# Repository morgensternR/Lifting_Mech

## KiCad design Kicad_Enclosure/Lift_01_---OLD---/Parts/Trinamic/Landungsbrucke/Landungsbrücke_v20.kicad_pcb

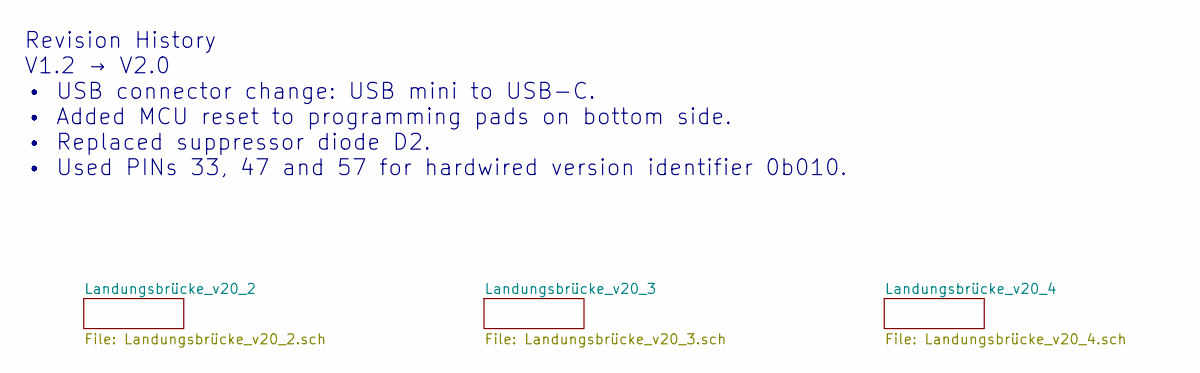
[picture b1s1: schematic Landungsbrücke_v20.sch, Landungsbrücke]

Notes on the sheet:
Revision History V1.2 → V2.0 • USB connector change: USB mini to USB-C. • Added MCU reset to programming pads on bottom side. • Replaced suppressor diode D2. • Used PINs 33, 47 and 57 for hardwired version identifier 0b010.

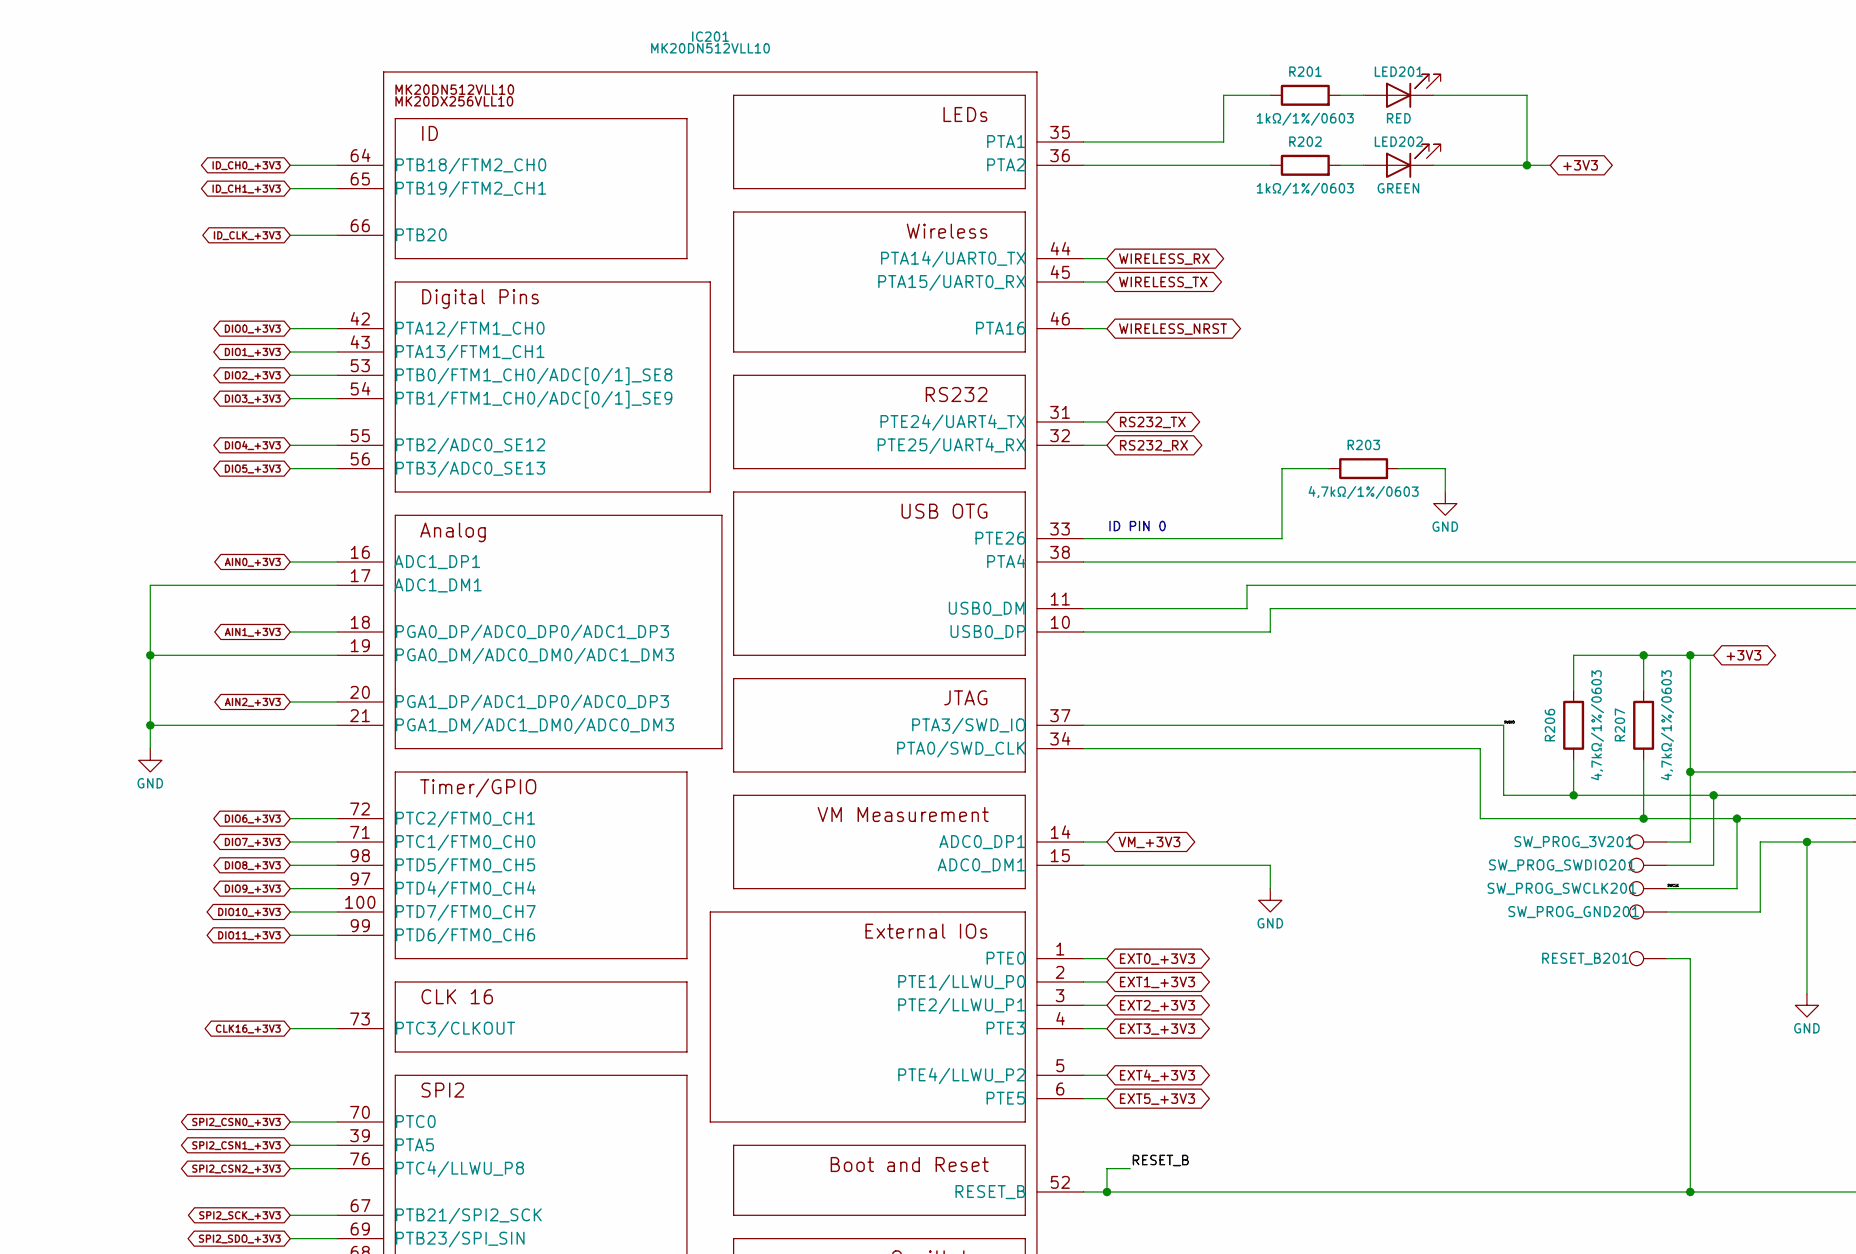
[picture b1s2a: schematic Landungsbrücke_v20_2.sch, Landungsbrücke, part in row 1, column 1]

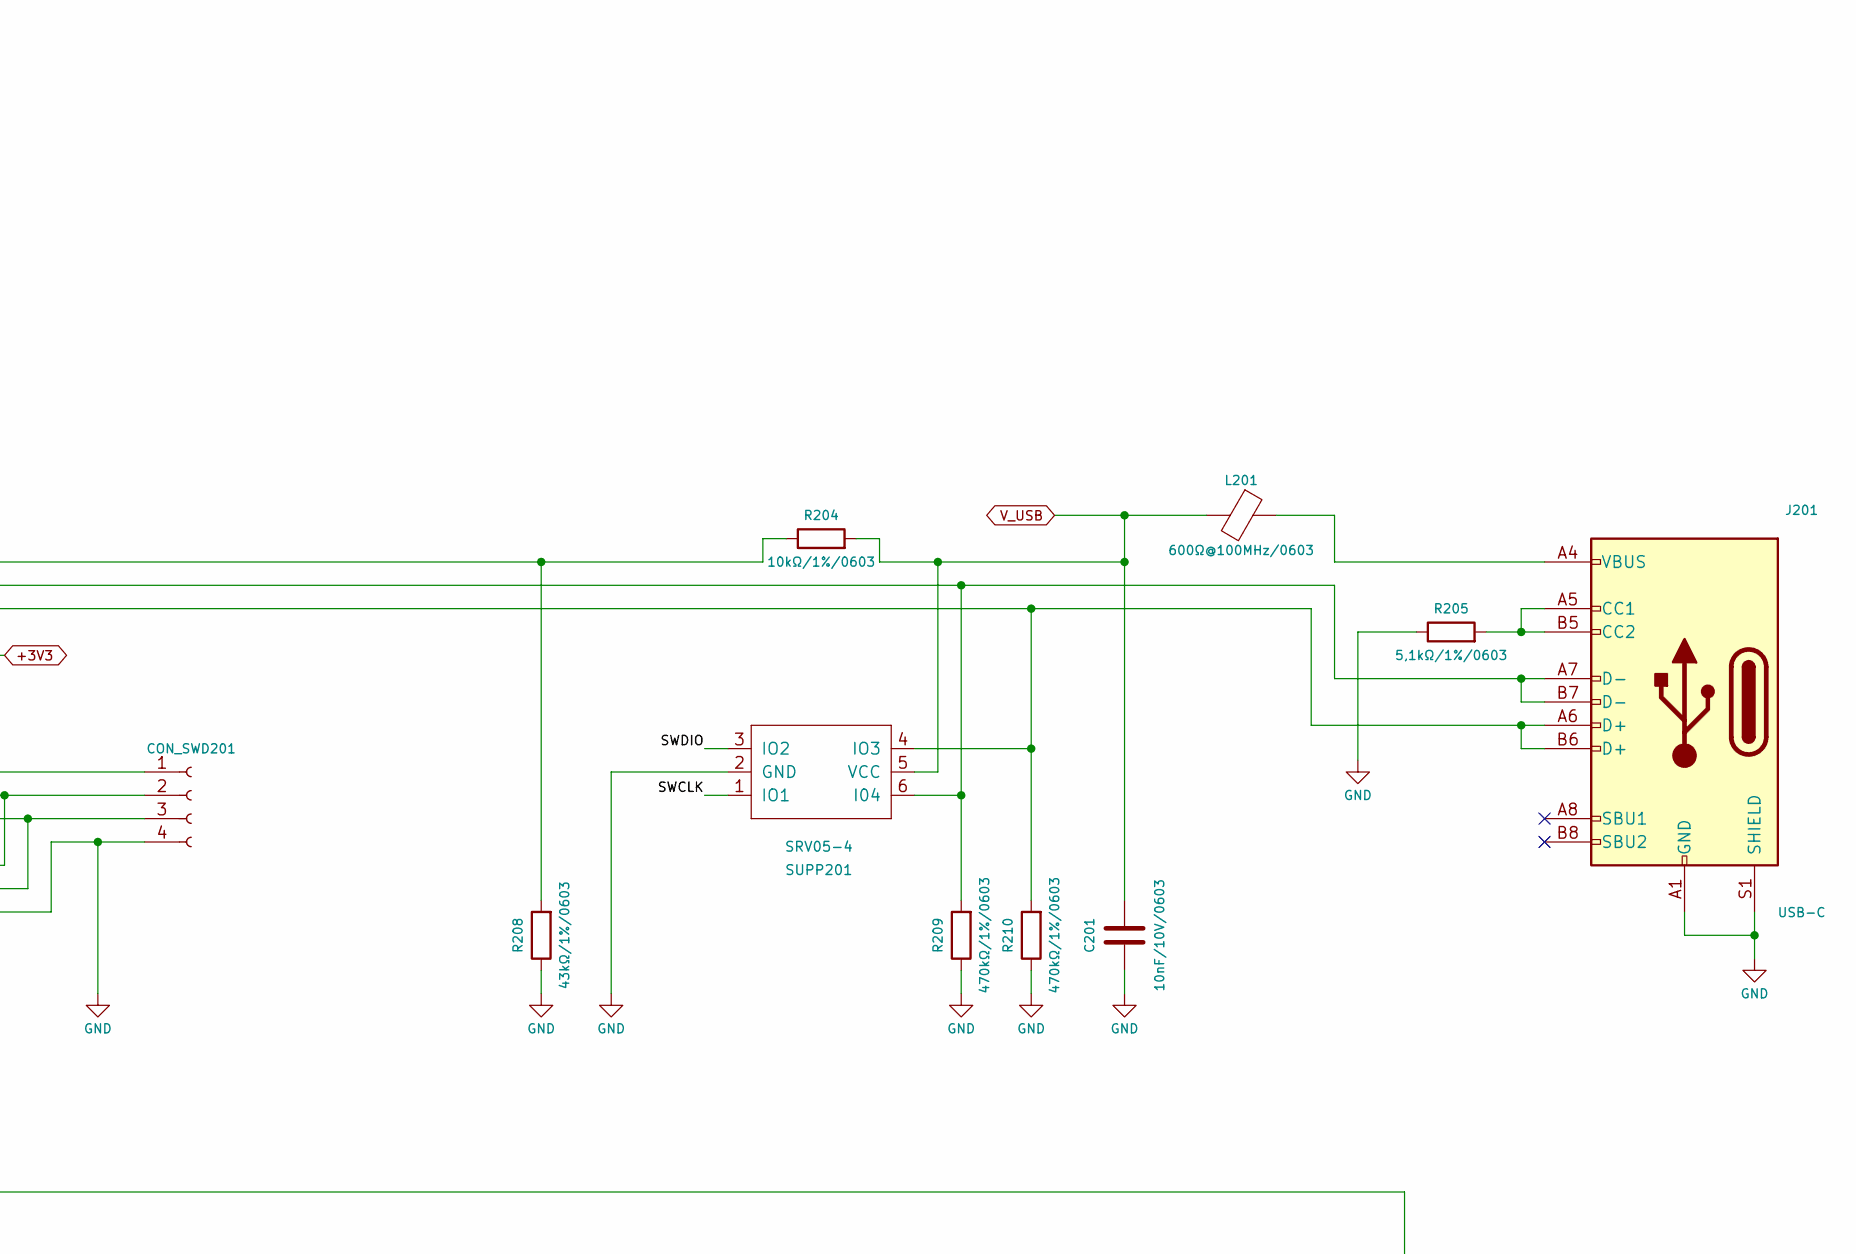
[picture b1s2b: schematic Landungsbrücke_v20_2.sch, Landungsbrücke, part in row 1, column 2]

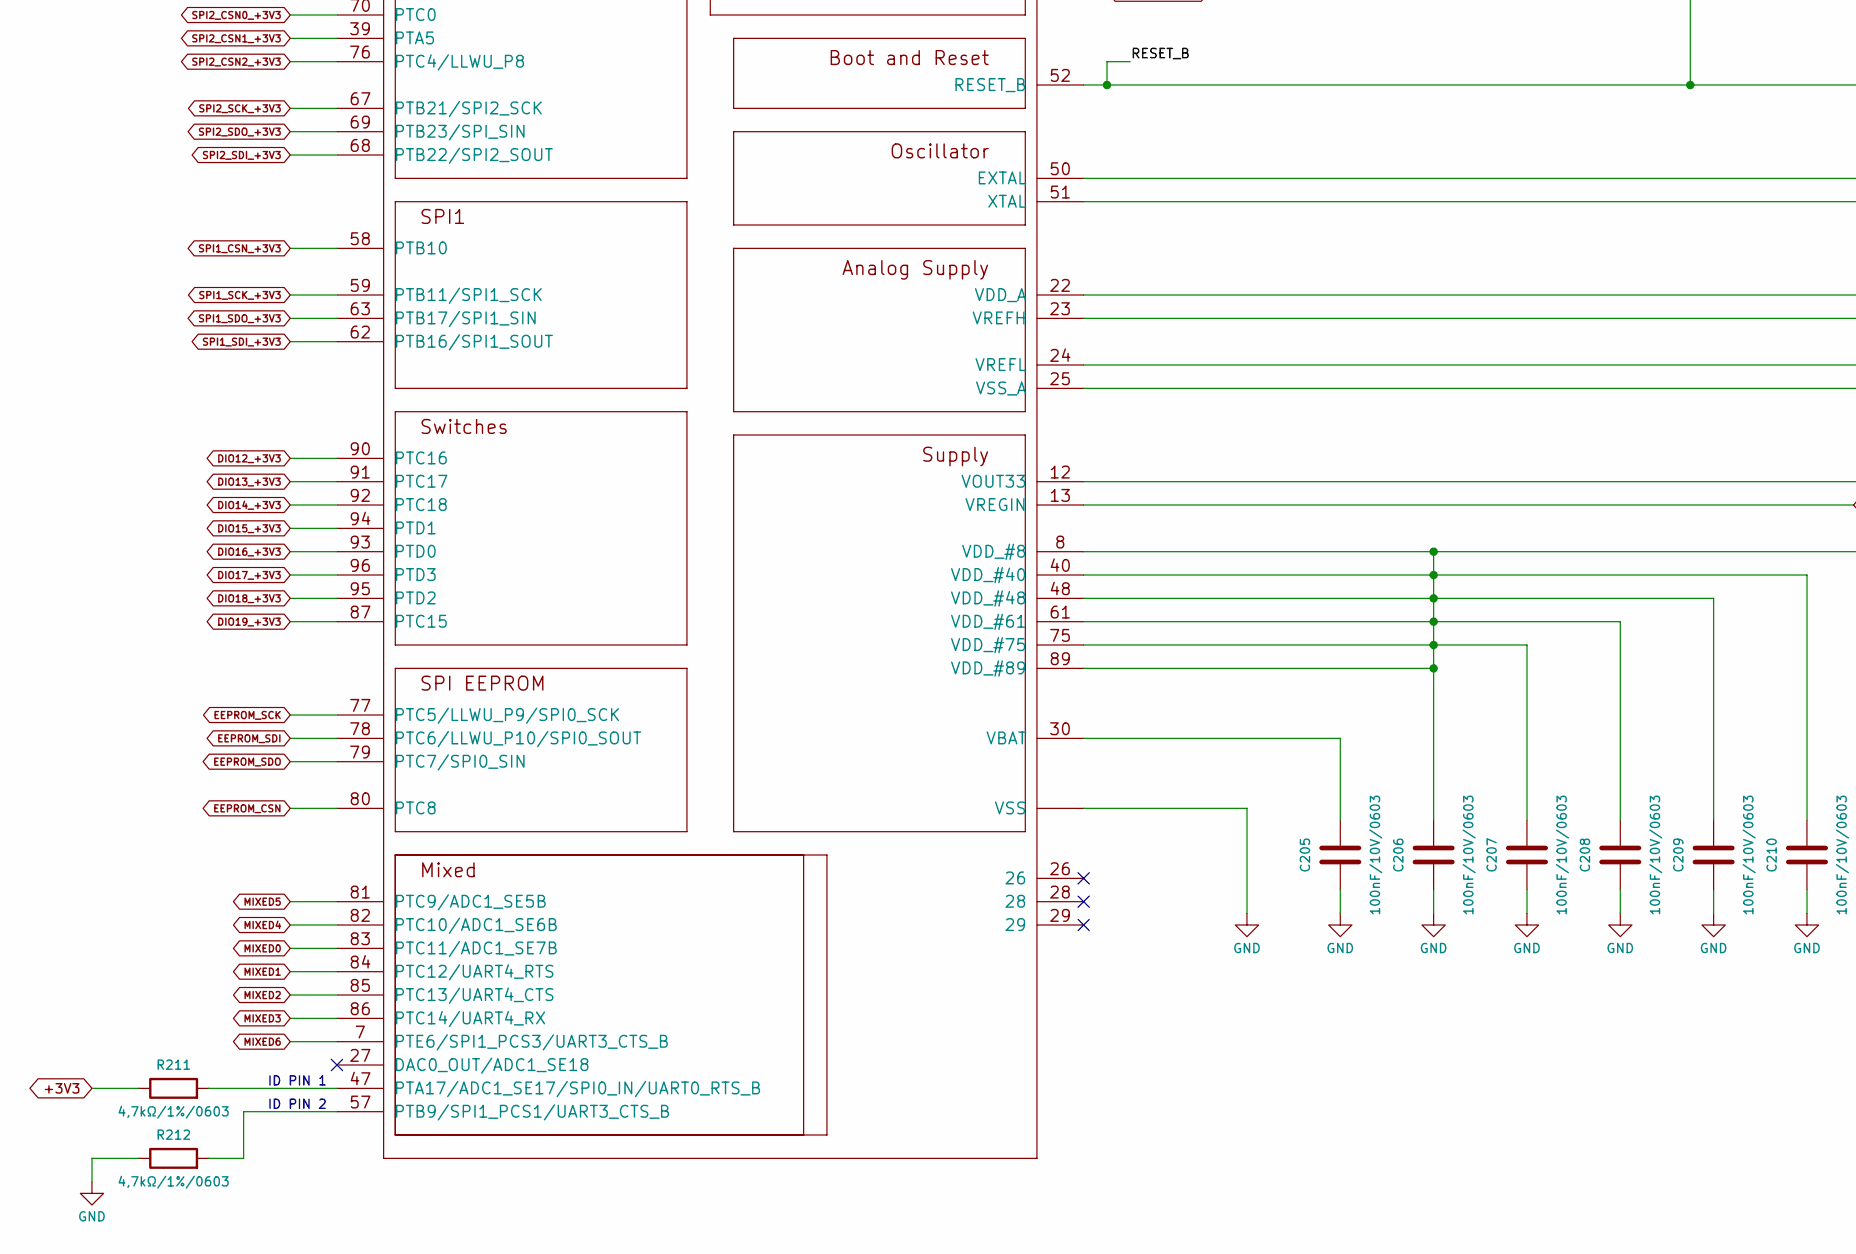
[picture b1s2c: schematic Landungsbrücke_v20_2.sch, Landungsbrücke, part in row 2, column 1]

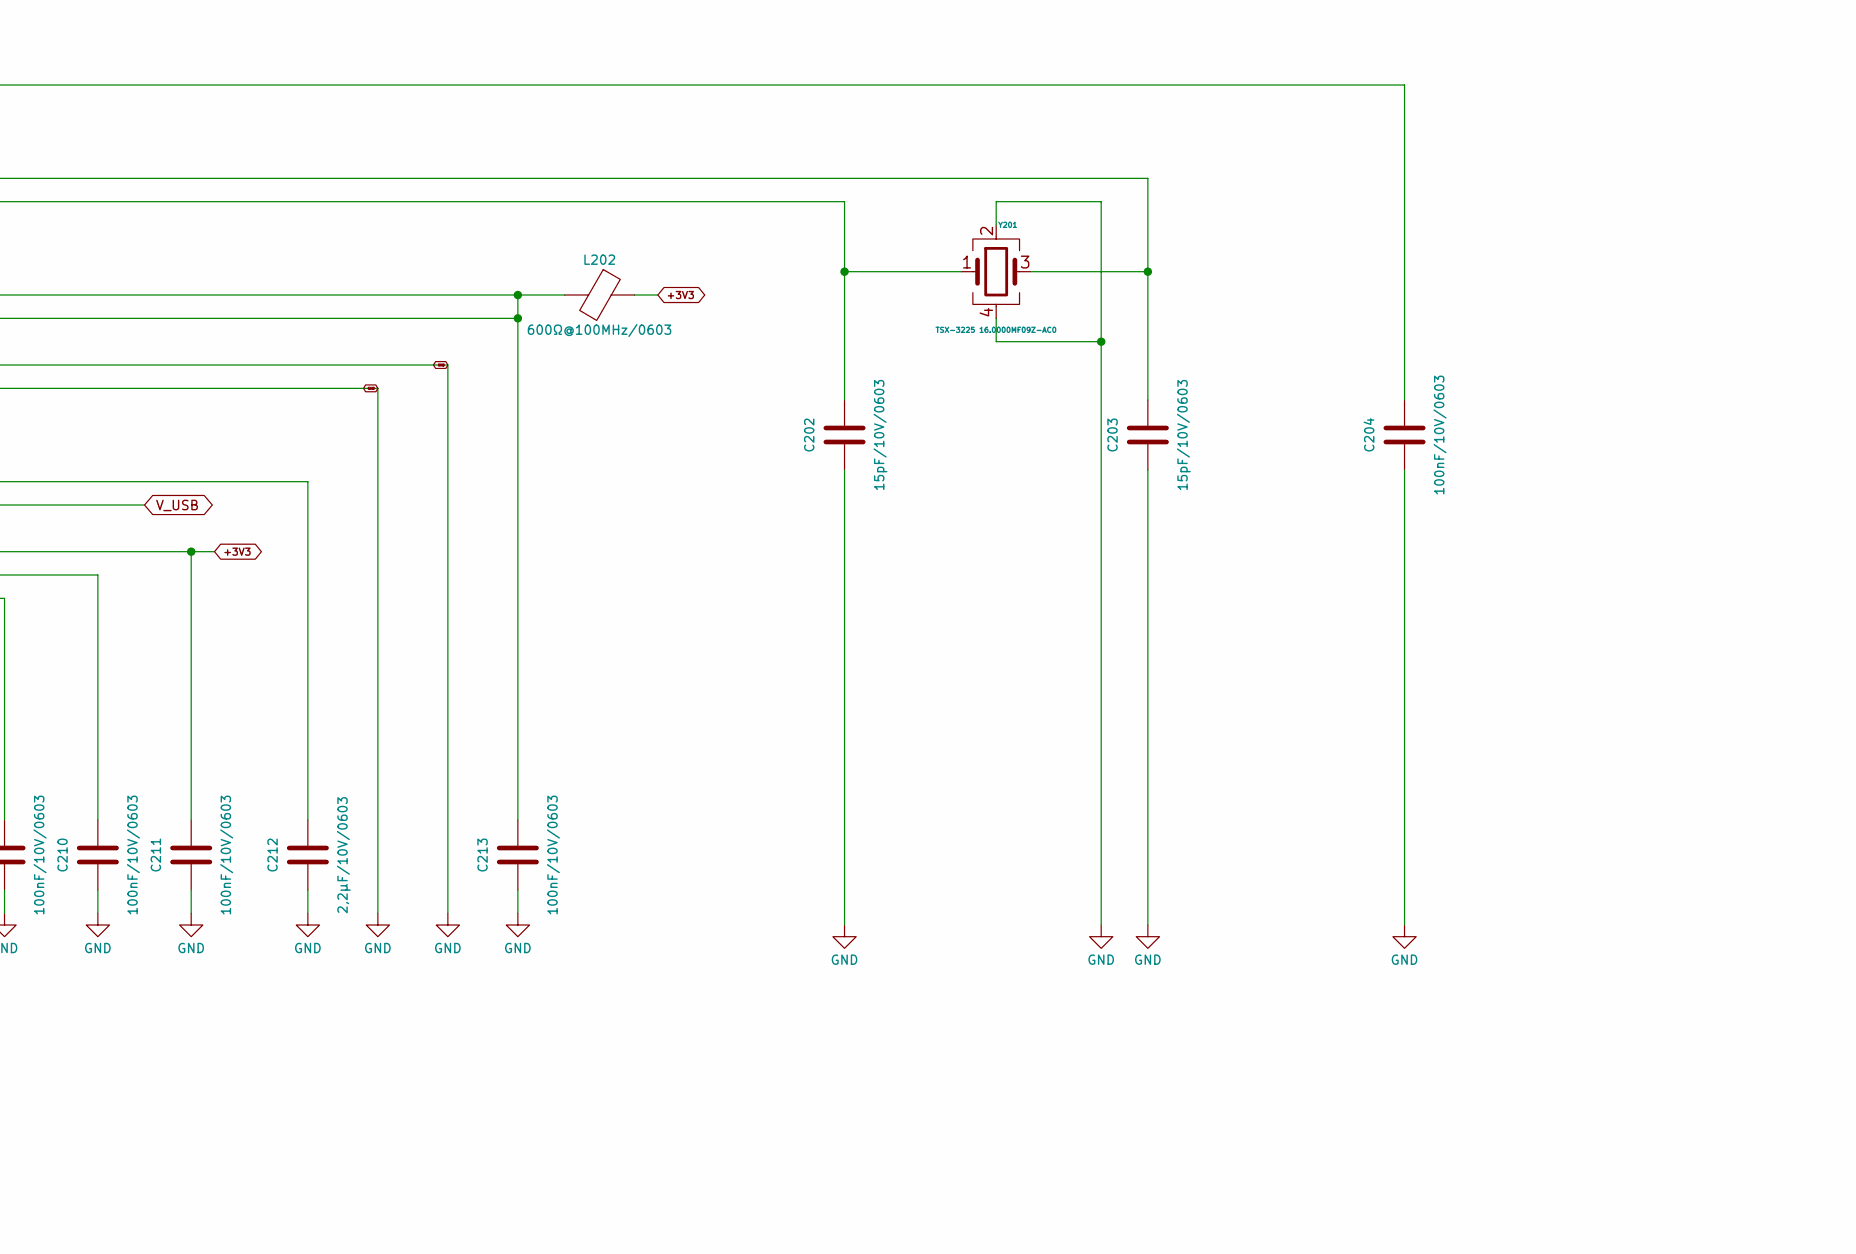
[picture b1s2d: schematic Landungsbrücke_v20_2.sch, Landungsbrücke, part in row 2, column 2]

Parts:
C201: 10nF/10V/0603; C_0603_1608Metric
C202, C203: 15pF/10V/0603; C_0603_1608Metric
C204, C205, C206, C207, C208, C209, C210, C211, C213: 100nF/10V/0603; C_0603_1608Metric
C212: 2,2µF/10V/0603; C_0603_1608Metric
CON_SWD201: PinSocket_1x04_P2.54mm_Vertical_SMD_Pin1Right
IC201: MK20DN512VLL10; LQFP-100_14x14mm_P0.5mm
J201: USB-C; USB_C_Molex_1054500101_Horisontal
L201, L202: 600Ω@100MHz/0603; L_0603_1608Metric
LED201: RED; LED_0603_1608Metric
LED202: GREEN; LED_0603_1608Metric
R201, R202: 1kΩ/1%/0603; R_0603_1608Metric
R203, R206, R207, R211, R212: 4,7kΩ/1%/0603; R_0603_1608Metric
R204: 10kΩ/1%/0603; R_0603_1608Metric
R205: 5,1kΩ/1%/0603; R_0603_1608Metric
R208: 43kΩ/1%/0603; R_0603_1608Metric
R209, R210: 470kΩ/1%/0603; R_0603_1608Metric
RESET_B201: Not assembled; TestPoint_Pad_D1.5mm
SUPP201: SRV05-4; SOT-23-6
SW_PROG_3V201: Not assembled; TestPoint_Pad_D1.5mm
SW_PROG_GND201: Not assembled; TestPoint_Pad_D1.5mm
SW_PROG_SWCLK201: Not assembled; TestPoint_Pad_D1.5mm
SW_PROG_SWDIO201: Not assembled; TestPoint_Pad_D1.5mm
Y201: TSX-3225 16.0000MF09Z-AC0; Crystal_SMD_SeikoEpson_FA238V-4Pin_3.2x2.5mm

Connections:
+3V3: C206.2, C207.2, C208.2, C209.2, C210.2, C211.1, CON_SWD201.1, IC201.8 (VDD_#8), IC201.40 (VDD_#40), IC201.48 (VDD_#48), IC201.61 (VDD_#61), IC201.75 (VDD_#75), IC201.89 (VDD_#89), L202.1, LED201.1 (K), LED202.1 (K), R206.2, R207.2, R211.1, SW_PROG_3V201.1; also elsewhere on the board
/Landungsbrücke_v20_2/RESET_B: C204.2, IC201.52 (RESET_B), RESET_B201.1
/Landungsbrücke_v20_2/SWCLK: CON_SWD201.3, IC201.34 (PTA0/SWD_CLK), R207.1, SUPP201.1 (IO1), SW_PROG_SWCLK201.1
/Landungsbrücke_v20_2/SWDIO: CON_SWD201.2, IC201.37 (PTA3/SWD_IO), R206.1, SUPP201.3 (IO2), SW_PROG_SWDIO201.1
AIN0_+3V3: IC201.16 (ADC1_DP1); also elsewhere on the board
AIN1_+3V3: IC201.18 (PGA0_DP/ADC0_DP0/ADC1_DP3); also elsewhere on the board
AIN2_+3V3: IC201.20 (PGA1_DP/ADC1_DP0/ADC0_DP3); also elsewhere on the board
CLK16_+3V3: IC201.73 (PTC3/CLKOUT); also elsewhere on the board
DIO0_+3V3: IC201.42 (PTA12/FTM1_CH0); also elsewhere on the board
DIO1_+3V3: IC201.43 (PTA13/FTM1_CH1); also elsewhere on the board
DIO2_+3V3: IC201.53 (PTB0/FTM1_CH0/ADC[0/1]_SE8); also elsewhere on the board
DIO3_+3V3: IC201.54 (PTB1/FTM1_CH0/ADC[0/1]_SE9); also elsewhere on the board
DIO4_+3V3: IC201.55 (PTB2/ADC0_SE12); also elsewhere on the board
DIO5_+3V3: IC201.56 (PTB3/ADC0_SE13); also elsewhere on the board
DIO6_+3V3: IC201.72 (PTC2/FTM0_CH1); also elsewhere on the board
DIO7_+3V3: IC201.71 (PTC1/FTM0_CH0); also elsewhere on the board
DIO8_+3V3: IC201.98 (PTD5/FTM0_CH5); also elsewhere on the board
DIO9_+3V3: IC201.97 (PTD4/FTM0_CH4); also elsewhere on the board
DIO10_+3V3: IC201.100 (PTD7/FTM0_CH7); also elsewhere on the board
DIO11_+3V3: IC201.99 (PTD6/FTM0_CH6); also elsewhere on the board
DIO12_+3V3: IC201.90 (PTC16); also elsewhere on the board
DIO13_+3V3: IC201.91 (PTC17); also elsewhere on the board
DIO14_+3V3: IC201.92 (PTC18); also elsewhere on the board
DIO15_+3V3: IC201.94 (PTD1); also elsewhere on the board
DIO16_+3V3: IC201.93 (PTD0); also elsewhere on the board
DIO17_+3V3: IC201.96 (PTD3); also elsewhere on the board
DIO18_+3V3: IC201.95 (PTD2); also elsewhere on the board
DIO19_+3V3: IC201.87 (PTC15); also elsewhere on the board
EEPROM_CSN: IC201.80 (PTC8); also elsewhere on the board
EEPROM_SCK: IC201.77 (PTC5/LLWU_P9/SPI0_SCK); also elsewhere on the board
EEPROM_SDI: IC201.78 (PTC6/LLWU_P10/SPI0_SOUT); also elsewhere on the board
EEPROM_SDO: IC201.79 (PTC7/SPI0_SIN); also elsewhere on the board
EXT0_+3V3: IC201.1 (PTE0); also elsewhere on the board
EXT1_+3V3: IC201.2 (PTE1/LLWU_P0); also elsewhere on the board
EXT2_+3V3: IC201.3 (PTE2/LLWU_P1); also elsewhere on the board
EXT3_+3V3: IC201.4 (PTE3); also elsewhere on the board
EXT4_+3V3: IC201.5 (PTE4/LLWU_P2); also elsewhere on the board
EXT5_+3V3: IC201.6 (PTE5); also elsewhere on the board
GND: C201.2, C202.1, C203.1, C204.1, C205.1, C206.1, C207.1, C208.1, C209.1, C210.1, C211.2, C212.2, C213.1, CON_SWD201.4, IC201.9 (VSS), IC201.15 (ADC0_DM1), IC201.17 (ADC1_DM1), IC201.19 (PGA0_DM/ADC0_DM0/ADC1_DM3), IC201.21 (PGA1_DM/ADC1_DM0/ADC0_DM3), IC201.24 (VREFL), IC201.25 (VSS_A), IC201.41 (VSS), IC201.49 (VSS), IC201.60 (VSS), IC201.74 (VSS), IC201.88 (VSS), J201.A1 (GND), J201.A12 (GND), J201.B1 (GND), J201.B12 (GND), J201.S1 (SHIELD), R203.2, R205.1, R208.1, R209.1, R210.1, R212.1, SUPP201.2 (GND), SW_PROG_GND201.1, Y201.2, Y201.4; also elsewhere on the board
ID_CH0_+3V3: IC201.64 (PTB18/FTM2_CH0); also elsewhere on the board
ID_CH1_+3V3: IC201.65 (PTB19/FTM2_CH1); also elsewhere on the board
ID_CLK_+3V3: IC201.66 (PTB20); also elsewhere on the board
MIXED0: IC201.83 (PTC11/ADC1_SE7B); also elsewhere on the board
MIXED1: IC201.84 (PTC12/UART4_RTS); also elsewhere on the board
MIXED2: IC201.85 (PTC13/UART4_CTS); also elsewhere on the board
MIXED3: IC201.86 (PTC14/UART4_RX); also elsewhere on the board
MIXED4: IC201.82 (PTC10/ADC1_SE6B); also elsewhere on the board
MIXED5: IC201.81 (PTC9/ADC1_SE5B); also elsewhere on the board
MIXED6: IC201.7 (PTE6/SPI1_PCS3/UART3_CTS_B); also elsewhere on the board
unnamed: C202.2, IC201.51 (XTAL), Y201.1
unnamed: C203.2, IC201.50 (EXTAL), Y201.3
unnamed: C205.2, IC201.30 (VBAT)
unnamed: C212.1, IC201.12 (VOUT33)
unnamed: C213.2, IC201.22 (VDD_A), IC201.23 (VREFH), L202.2
unnamed: IC201.10 (USB0_DP), J201.A6 (D+), J201.B6 (D+), R210.2, SUPP201.4 (IO3)
unnamed: IC201.11 (USB0_DM), J201.A7 (D-), J201.B7 (D-), R209.2, SUPP201.6 (I04)
unnamed: IC201.33 (PTE26), R203.1
unnamed: IC201.35 (PTA1), R201.1
unnamed: IC201.36 (PTA2), R202.1
unnamed: IC201.38 (PTA4), R204.1, R208.2
unnamed: IC201.47 (PTA17/ADC1_SE17/SPI0_IN/UART0_RTS_B), R211.2
unnamed: IC201.57 (PTB9/SPI1_PCS1/UART3_CTS_B), R212.2
unnamed: J201.A4 (VBUS), J201.A9 (VBUS), J201.B4 (VBUS), J201.B9 (VBUS), L201.1
unnamed: J201.A5 (CC1), J201.B5 (CC2), R205.2
unnamed: LED201.2 (A), R201.2
unnamed: LED202.2 (A), R202.2
RS232_RX: IC201.32 (PTE25/UART4_RX); also elsewhere on the board
RS232_TX: IC201.31 (PTE24/UART4_TX); also elsewhere on the board
SPI1_CSN_+3V3: IC201.58 (PTB10); also elsewhere on the board
SPI1_SCK_+3V3: IC201.59 (PTB11/SPI1_SCK); also elsewhere on the board
SPI1_SDI_+3V3: IC201.62 (PTB16/SPI1_SOUT); also elsewhere on the board
SPI1_SDO_+3V3: IC201.63 (PTB17/SPI1_SIN); also elsewhere on the board
SPI2_CSN0_+3V3: IC201.70 (PTC0); also elsewhere on the board
SPI2_CSN1_+3V3: IC201.39 (PTA5); also elsewhere on the board
SPI2_CSN2_+3V3: IC201.76 (PTC4/LLWU_P8); also elsewhere on the board
SPI2_SCK_+3V3: IC201.67 (PTB21/SPI2_SCK); also elsewhere on the board
SPI2_SDI_+3V3: IC201.68 (PTB22/SPI2_SOUT); also elsewhere on the board
SPI2_SDO_+3V3: IC201.69 (PTB23/SPI_SIN); also elsewhere on the board
VM_+3V3: IC201.14 (ADC0_DP1); also elsewhere on the board
V_USB: C201.1, IC201.13 (VREGIN), L201.2, R204.2, SUPP201.5 (VCC); also elsewhere on the board
WIRELESS_NRST: IC201.46 (PTA16); also elsewhere on the board
WIRELESS_RX: IC201.44 (PTA14/UART0_TX); also elsewhere on the board
WIRELESS_TX: IC201.45 (PTA15/UART0_RX); also elsewhere on the board

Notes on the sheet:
ID PIN 0
ID PIN 1
ID PIN 2
